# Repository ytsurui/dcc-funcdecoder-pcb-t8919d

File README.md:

# DCC Function Decoder PCB Data for TOMIX 8919

NMRA規格の信号を受信して動作する、ファンクション専用のDCCデコーダの基板設計データです。

TOMIX製Nゲージ鉄道模型に搭載されている、8919と刻印されている基板と交換してそのまま搭載可能な設計となっております。

回路図、基板設計データ、面付け済みの設計データを含みます。
<br>面付け済みのデータについては、ガーバーデータも含みます。 (elecrowにて製造できることを確認済み)

## 取り扱い上の注意点

  * 基板設計ミスがあるため、現在の設計データのまま製造した場合、取付穴径を3.8mm程度に開けなおす必要があります。<br>この問題点はRev.1以降のリリースで修正予定です。

### 主要スペック
  * 組み立て後の基板サイズ: 17.5mm x 14.5mm x 2.6mm
  * TOMIX製Nゲージ鉄道模型に搭載されている、8919と刻印されている基板と差し替えて取り付け可能
  * 基板表面にヘッドライト用、裏面にテールライト用のLEDを実装可能<br>(LEDは面実装タイプ)
  * MOSFETを追加で実装することで、追加のファンクションを1つ配線可能
  * ヘッドライトとテールライトの回路については、定電流回路を搭載し、一定の照度でLEDを点灯可能
  * マイコンプログラム書き込み用端子を装備し、ピンヘッダを使用した簡単な治具でAVRライタと接続し、ファームウェアを変更可能

### 対応するファームウェア
  * [Atmel ATtiny45 DCC Function Decoder Firmware](https://github.com/ytsurui/dcc-funcdecoder-firmware)

### 各種ドキュメント

  * [パーツリスト](docs/partslist.md)

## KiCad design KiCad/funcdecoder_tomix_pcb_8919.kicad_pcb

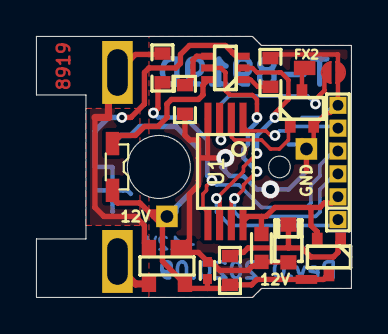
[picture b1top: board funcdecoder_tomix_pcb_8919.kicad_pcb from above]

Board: 2 copper layers, 17.5 x 14.5 mm, 24 parts (1 on the bottom side), 17 nets.

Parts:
C1: 104; C_1005
C2: 226; C_1608
D1: BAS3007; SOT-143
D2: 5.1V; UMD2
D3, D4: LED; LED_1224_SIDE
H**: HOLE_1.2mm
H**#2: HOLE_3.5mm
J1: PROG; PAD_PROG_6PIN_HOLE0.6
J2, J3: RAIL; TOMIX_CONTACT_HOLE
PAD1: 12V; PAD_1.2x1.2_Hole0.7
PAD2: GND; PAD_1.2x1.2_Hole0.7
PAD3: 12V; PAD_0.5x1.2_SMD
PAD4: FX2; PAD_1.2x0.8_SMD
PAD5: DIR; SOLDER_CONN_PAD_1.5mm
Q1: 2SC4116; SC-70
Q2: 2N7002DW; SOT-363-nomark
Q3: SSM3K7002BFU; SC-70
R1: 103; R_1608
R2, R3: 102; R_1608
R4: 104; R_1608
U1: ATtiny45-20SU; TSSOP-8

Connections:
+5V: C2.1, J1.2, Q1.2, U1.8
+12V: C1.1, D1.4, D3.2, D4.2, PAD1.1, PAD3.1, Q1.3, R1.1
DIR_JP: PAD5.1, U1.3
FX2: PAD4.1, Q3.3
Func1_For: J1.1, Q2.2, U1.6
Func1_Rev: J1.3, Q2.5, U1.7
Func2: Q3.1, U1.2
GND: C1.2, C2.2, D1.1, D2.2, J1.6, PAD2.1, PAD5.2, Q3.2, R2.2, R3.2, U1.4
MOSI: J1.4, R4.2, U1.5
unnamed: D2.1, Q1.1, R1.2
unnamed: D3.1, Q2.6
unnamed: D4.1, Q2.3
unnamed: Q2.1, R2.1
unnamed: Q2.4, R3.1
RAIL+: D1.2, J2.1, R4.1
RAIL-: D1.3, J3.1
RESET: J1.5, U1.1
